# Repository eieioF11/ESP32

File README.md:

# ESP32
ESP-WROOM-32というWifiとBluetooth搭載のマイコンを使用したプログラムのリポジトリ
# フォルダ構成
- example  :ESP32のプログラムの例
- hardware :対向二輪ロボットやアームの設計データ、ESP32を使用した基板のデータ
- image    :写真や動画データなど
- library  :projectsのプログラムで使用しているライブラリー
- projects :対向二輪ロボットのプログラムやアームのプログラムなど
  - ROBOCON:NHK高専ロボコン時に作成したproject
# 開発に使用したソフト
- ソフトウェア開発
  - Visual Studio Code
  - PlatformIO
- ハードウェア開発
  - 基板製作:Autodesk Eagle
  - 筐体制作:Autodesk Fusion360,Inventor
# Opposing two wheels
制御練習用の対向二輪の足回り。専用のコントローラーまたはスマホからコントロールできる。

- ライントレース  

- 台形制御

# Mini arm robot
3Dプリンターとサーボモーター（sg90）で作成した。

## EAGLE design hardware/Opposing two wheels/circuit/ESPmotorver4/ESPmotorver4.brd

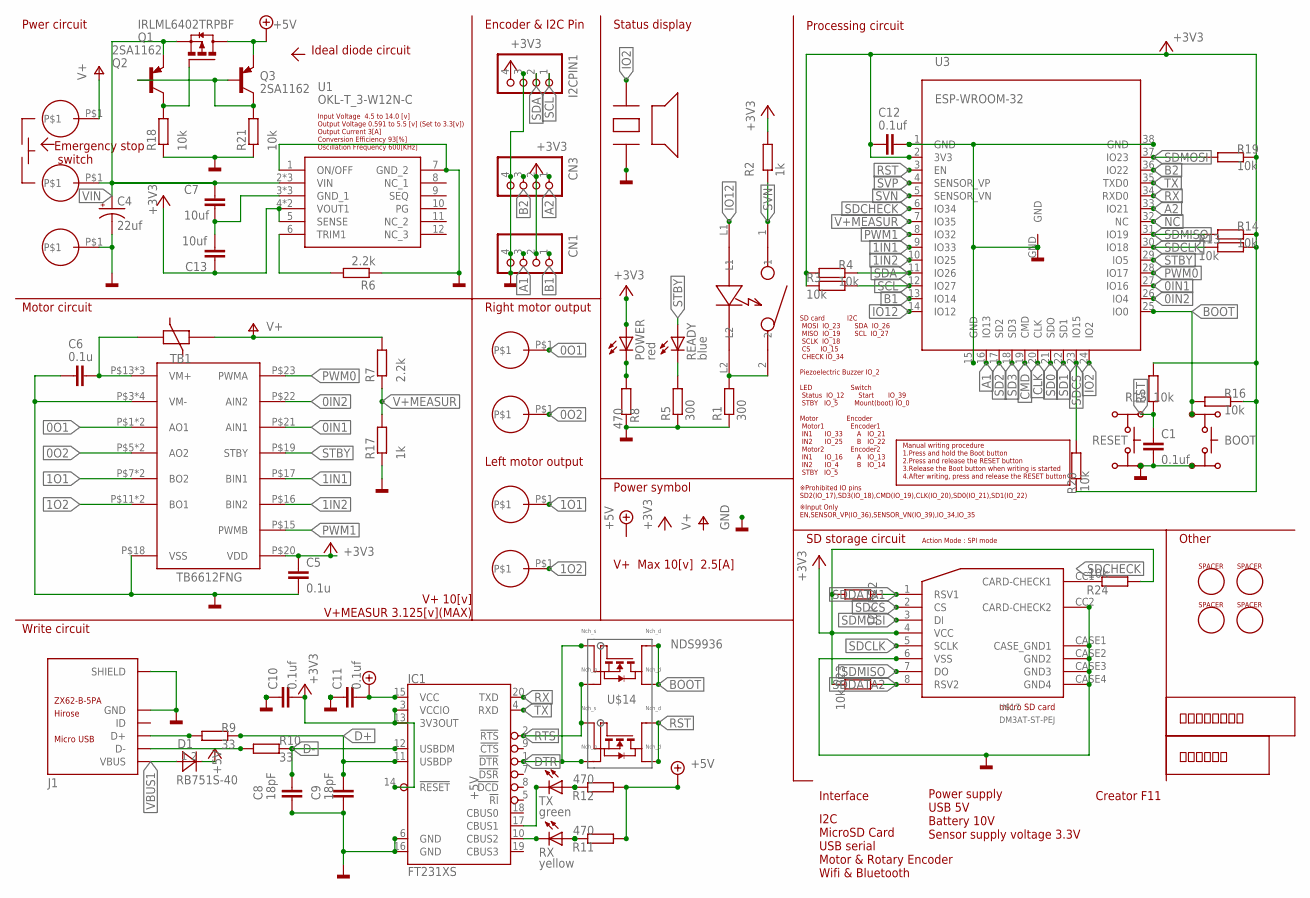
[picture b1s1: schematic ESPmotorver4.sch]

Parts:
BOOT: TACTSWITCH-4PSKRP; SKRP
C1, C10, C11, C12: 0.1uf; C0603K
C4: 22uf; CT3528
C5, C6: 0.1u; C0603
C7, C13: 10uf; C0805
C8, C9: 18pF; C0603
CN1, CN3: S4B-XH-A
D1: RB751S-40; EMD2
EM: PV-3
GND: PV-3
I2CPIN1: S4B-XH-A
IC1: FT231XS; SSOP20
J1: ZX62-B-5PA; ZX62-B-5PA(11)
POWER: red; CHIPLED_0805
Q1: IRLML6402TRPBF; SOT23
Q2, Q3: 2SA1162; SC59-BEC
R1, R5: 300; R0603
R2, R17: 1k; R0603
R3, R4, R13, R14, R15, R16, R18, R19, R20, R21, R22, R23, R24: 10k; R0603
R6, R7: 2.2k; R0603
R8, R11, R12: 470; R0603
R9, R10: 33; R0603
READY: blue; CHIPLED_0805
RESET: TACTSWITCH-4PSKRP; SKRP
RX: yellow; CHIPLED_0805
SW: TSHD-T2.8T2; LEDSWITCH
TB1: TB6612FNG
TX: green; CHIPLED_0805
U1: OKL-T_3-W12N-C; OKL-T3-W12
U3: ESP-WROOM-32
U$1: SCHOOLMARK1
U$3: SCHOOLMARK2
U$6: PKLCS1212E4001-R1; SMD_SOUNDER
U$7, U$9, U$10, U$15: PV-3
U$8, U$11, U$12, U$13: SPACER
U$14: NDS9936; SO-8
U$16: SMD1812
U$17: DM3AT-ST-PEJ; DM3AT-SF-PEJ
VIN: PV-3

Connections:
0IN1: TB1.P$21 (AIN1), U3.27 (IO16)
0IN2: TB1.P$22 (AIN2), U3.26 (IO4)
0O1: TB1.P$1 (AO1), TB1.P$2 (AO1), U$7.P$1
0O2: TB1.P$5 (AO2), TB1.P$6 (AO2), U$9.P$1
1IN1: TB1.P$17 (BIN1), U3.9 (IO33)
1IN2: TB1.P$16 (BIN2), U3.10 (IO25)
1O1: TB1.P$7 (BO2), TB1.P$8 (BO2), U$10.P$1
1O2: TB1.P$11 (BO1), TB1.P$12 (BO1), U$15.P$1
+3V3: C5.1, C10.2, C12.2, C13.1, CN1.2, CN3.2, I2CPIN1.4, IC1.3 (VCCIO), IC1.13 (3V3OUT), IC1.14 (!RESET), POWER.A, R2.2, R3.1, R4.1, R13.2, R14.2, R15.2, R16.2, R19.2, R20.1, R22.2, R23.2, R24.1, TB1.P$20 (VDD), U1.4 (VOUT1), U1.5 (SENSE), U1.17 (VOUT1), U3.2 (3V3), U$17.4 (VCC)
+5V: C11.2, D1.2 (C), IC1.15 (VCC), Q1.3 (D), Q3.E, R11.1, R12.1
A1: CN1.3, U3.16 (IO13)
A2: CN3.1, U3.33 (IO21)
B1: CN1.1, U3.13 (IO14)
B2: CN3.3, U3.36 (IO22)
BOOT: BOOT.4, R16.1, U3.25 (IO0), U$14.7, U$14.8
CLK: U3.20 (CLK)
CMD: U3.19 (CMD)
D+: C9.1, IC1.11 (USBDP), R9.2
D-: C8.1, IC1.12 (USBDM), R10.2
DTR: IC1.1 (!DTR), U$14.1, U$14.4
GND: BOOT.2, C1.2, C4.-, C5.2, C6.2, C7.2, C8.2, C9.2, C10.1, C11.1, C12.1, C13.2, CN1.4, CN3.4, GND.P$1, I2CPIN1.3, IC1.6 (GND), IC1.16 (GND), J1.5 (GND), J1.SH1 (SHIELD), J1.SH2 (SHIELD), J1.SH3 (SHIELD), J1.SH4 (SHIELD), J1.SH5 (SHIELD), J1.SH6 (SHIELD), R1.1, R5.1, R6.1, R8.2, R17.1, R18.1, R21.1, RESET.1, TB1.P$3 (VM-), TB1.P$4 (VM-), TB1.P$9 (VM-), TB1.P$10 (VM-), TB1.P$18 (VSS), U1.1 (ON/OFF), U1.3 (GND_1), U1.7 (GND_2), U1.15 (GND_1), U1.16 (GND_1), U3.1 (GND), U3.15 (GND), U3.38 (GND), U3.GND, U$6.P$2, U$17.6 (VSS), U$17.CASE1 (CASE_GND1), U$17.CASE2 (GND2), U$17.CASE3 (GND3), U$17.CASE4 (GND4), U$17.CC2 (CARD-CHECK2)
IO2: U3.24 (IO2), U$6.P$1
IO12: SW.L1, U3.14 (IO12)
unnamed: R1.2, SW.2, SW.L2
unnamed: J1.2 (D-), R10.1
unnamed: C6.1, TB1.P$13 (VM+), TB1.P$14 (VM+), TB1.P$24 (VM+), U$16.P$2
unnamed: R6.2, U1.6 (TRIM1)
unnamed: J1.3 (D+), R9.1
unnamed: Q2.B, Q3.B, Q3.C, R21.2
unnamed: R5.2, READY.C
unnamed: Q1.1 (G), Q2.C, R18.2
unnamed: R11.2, RX.A
unnamed: IC1.10 (CBUS2), RX.C
unnamed: R12.2, TX.A
unnamed: POWER.C, R8.1
unnamed: IC1.17 (CBUS1), TX.C
NC: U3.32 (NC)
PWM0: TB1.P$23 (PWMA), U3.28 (IO17)
PWM1: TB1.P$15 (PWMB), U3.8 (IO32)
RST: C1.1, R15.1, RESET.3, U3.3 (EN), U$14.5, U$14.6
RTS: IC1.2 (!RTS), U$14.2, U$14.3
RX: IC1.20 (TXD), U3.34 (RXD0)
SCL: I2CPIN1.1, R3.2, U3.12 (IO27)
SD0: U3.21 (SDO)
SD1: U3.22 (SD1)
SD2: U3.17 (SD2)
SD3: U3.18 (SD3)
SDA: I2CPIN1.2, R4.2, U3.11 (IO26)
SDCHECK: R24.2, U3.6 (IO34), U$17.CC1 (CARD-CHECK1)
SDCLK: R13.1, U3.30 (IO18), U$17.5 (SCLK)
SDCS: R20.2, U3.23 (IO15), U$17.2 (CS)
SDDATA1: R22.1, U$17.1 (RSV1)
SDDATA2: R23.1, U$17.8 (RSV2)
SDMISO: R14.1, U3.31 (IO19), U$17.7 (DO)
SDMOSI: R19.1, U3.37 (IO23), U$17.3 (DI)
STBY: READY.A, TB1.P$19 (STBY), U3.29 (IO5)
SVN: R2.1, SW.1, U3.5 (SENSOR_VN)
SVP: U3.4 (SENSOR_VP)
TX: IC1.4 (RXD), U3.35 (TXD0)
V+: EM.P$1, R7.2, U$16.P$1
V+MEASUR: R7.1, R17.2, U3.7 (IO35)
VBUS1: D1.1 (A), J1.1 (VBUS)
VIN: C4.+, C7.1, Q1.2 (S), Q2.E, U1.2 (VIN), U1.13 (VIN), U1.14 (VIN), VIN.P$1

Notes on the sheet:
Write circuit
Processing circuit
SD storage circuit
Pwer circuit
Motor circuit
Encoder & I2C Pin
Status display
Other
Power symbol
V+ Max 10[v] 2.5[A]
Right motor output
Left motor output
V+ 10[v] V+MEASUR 3.125[v](MAX)
Emergency stop switch
Interface
I2C MicroSD Card USB serial Motor & Rotary Encoder Wifi & Bluetooth
Power supply USB 5V Battery 10V Sensor supply voltage 3.3V
Creator F11
Ideal diode circuit
SD card I2C MOSI IO_23 SDA IO_26 MISO IO_19 SCL IO_27 SCLK IO_18 CS IO_15 CHECK IO_34 Piezoelectric Buzzer IO_2 LED Switch Status IO_12 Start IO_39 STBY IO_5 Mount(boot) IO_0 Motor Encoder Motor1 Encoder1 IN1 IO_33 A IO_21 IN2 IO_25 B IO_22 Motor2 Encoder2 IN1 IO_16 A IO_13 IN2 IO_4 B IO_14 STBY IO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
Manual writing procedure 1.Press and hold the Boot button 2.Press and release the RESET button 3.Release the Boot button when writing is started 4.After writing, press and release the RESET button
※Input Only EN,SENSOR_VP(IO_36),SENSOR_VN(IO_39),IO_34,IO_35
Input Voltage 4.5 to 14.0 [v] Output Voltage 0.591 to 5.5 [v] (Set to 3.3[v]) Output Current 3[A] Conversion Efficiency 93[%] Oscillation Frequency 600[KHz]
Action Mode : SPI mode

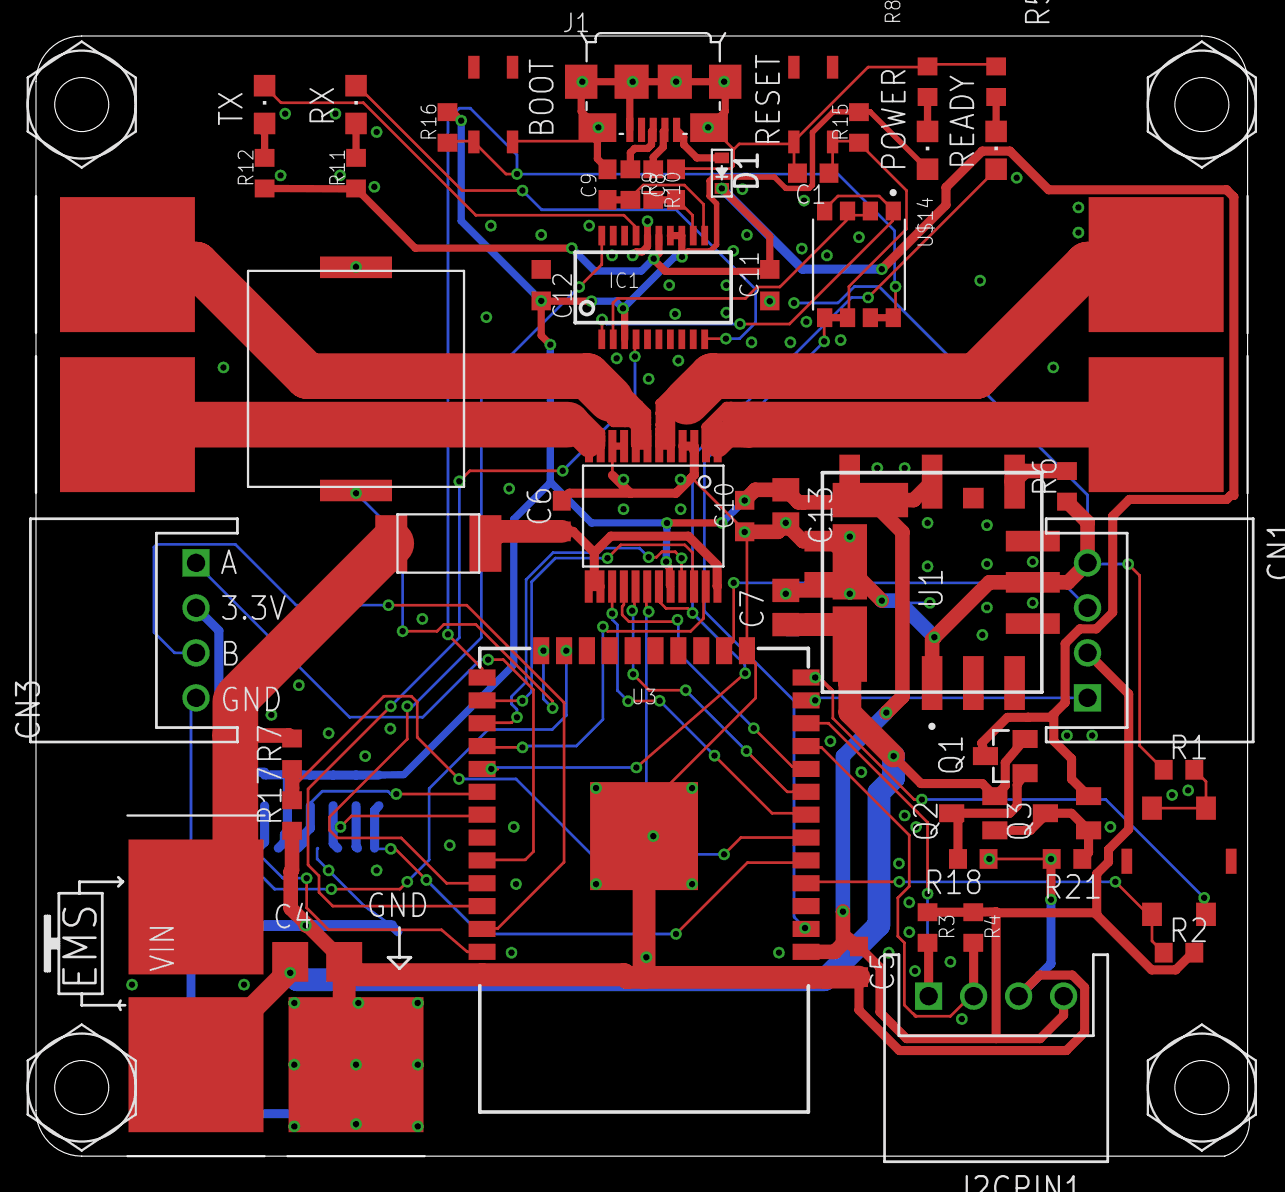
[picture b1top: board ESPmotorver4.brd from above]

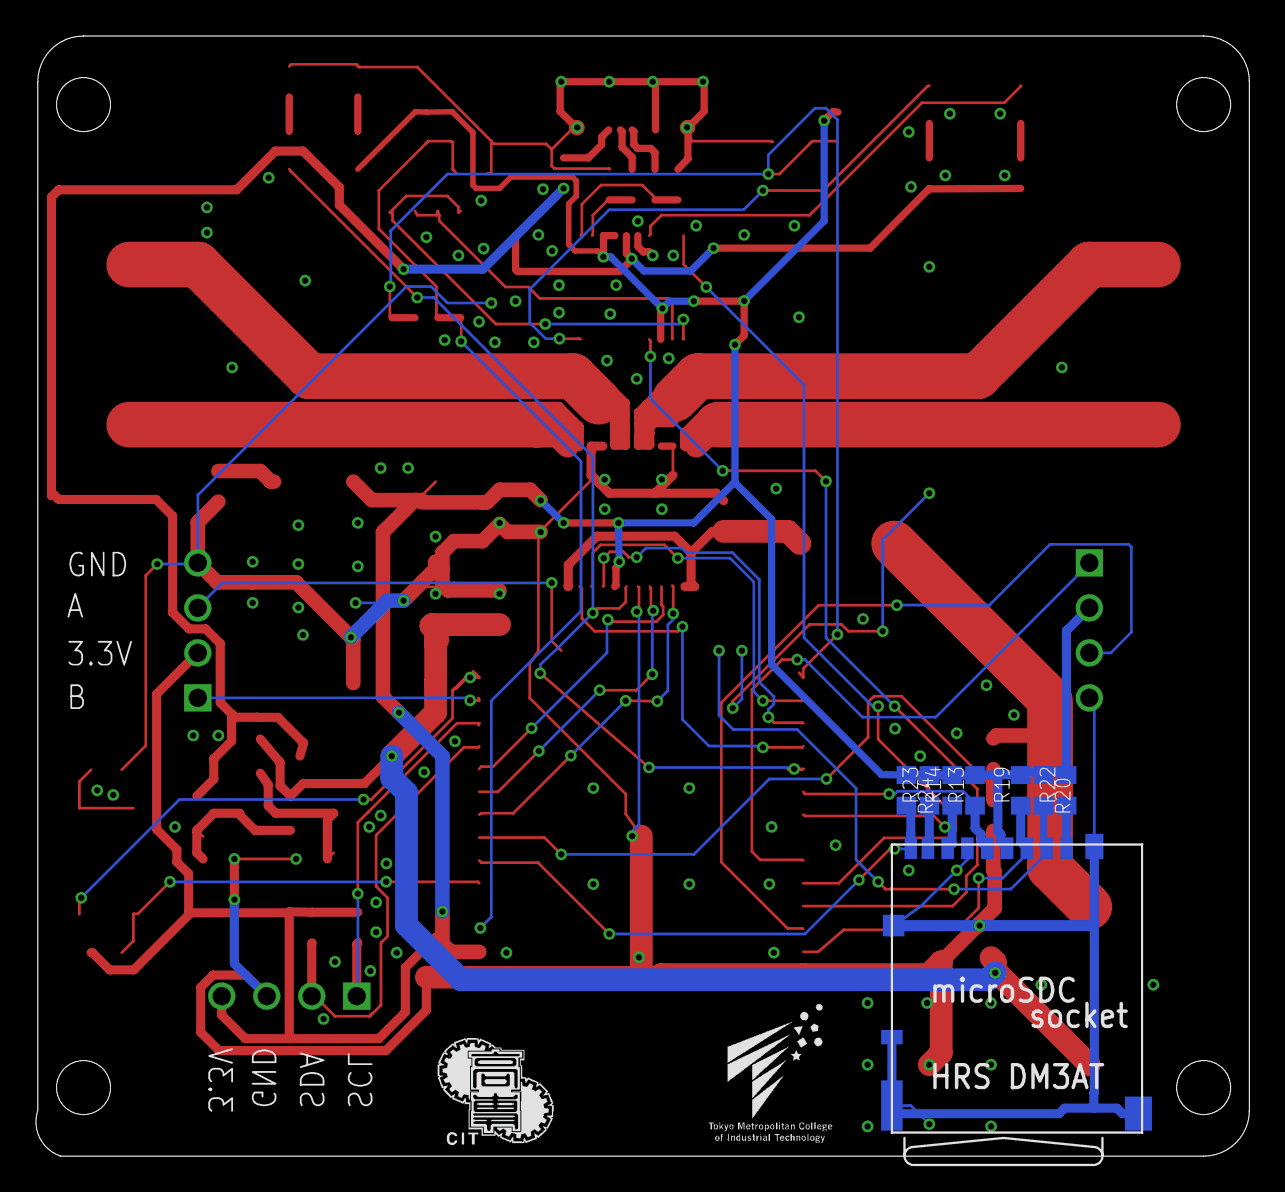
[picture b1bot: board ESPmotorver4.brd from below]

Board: 2 copper layers, 67.4 x 62.2 mm, 71 parts (10 on the bottom side), 55 nets.

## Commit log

2020-10-14 move library
2020-10-14 move other file
2020-10-14 Change of platformio.ini
2020-10-14 add example
2020-10-14 add hardware
2020-10-14 Add project
2020-10-14 add image
2020-10-18 ROBOCON project
2020-10-18 Changed to use in Robocon
2020-10-19 add servo test
2020-10-24 ROBOCONproject coordination
2020-10-24 BB8project coordination
2020-10-24 add arm project ver2
2020-10-27 add servospeed class
2020-10-28 add Servo move
2020-10-29 Create ESP32mather class
2020-10-30 Servo motor operation added
2020-10-30 add EmargencyStopfarmware project
2020-10-31 test EMS
2020-10-31 Remote emergency stop adjustment
2020-11-01 Servo motor operation change
2020-11-01 Change to use new board
2020-11-03 Robocon project adjustment
2020-11-07 Robocon movement adjustment
2020-11-10 PWM.h update
2020-11-10 Fixed so that no error occurs at runtime
2020-11-10 Fixed a bug in self-position estimation (opposite two wheels)
2020-11-10 none
2020-11-12 Changed the specifications of PID.h
2020-11-12 Creating a trapezoidal control program
2020-11-14 Angle calculation correction from the wheel
2020-11-14 Creating a trapezoidal control movement program for opposed motorcycles
2020-11-15 Trapezoid control test
2020-11-15 Added default offset value setting
2020-11-15 Added angle correction when moving in a straight line
2020-11-15 Gain adjustment
2021-04-11 add ROS firm
2021-04-11 cahnge ROS firm
2021-04-29 Send odometry to PC with ROSSerial
2021-04-29 Board protection
2021-05-01 Change gain setup
2021-05-12 Power supply monitoring function reimplementation
2021-05-12 Minimum motor output setting
2021-05-13 add Speed class
2021-05-13 change odom
2021-05-14 Battery warning function added
2021-05-15 add PS3control
2021-05-15 change BatteryLevel
2021-05-16 change Mag offset
2021-06-13 add arm farm ver3
2021-07-01 add ROS IMU node
2021-07-16 mpu9250 library update
2021-07-16 Board protection function added
2021-07-16 Posture rotation direction change
2021-07-16 Uncomment
2021-07-20 Correct mistakes
2021-08-04 update ros firm
2022-01-02 [add]added new project
